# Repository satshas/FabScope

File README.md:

# Fab Scope

An easily fabbable and portable oscilloscope.

Features
--

- 2 voltage range supported: 0-5V, 0-50V (DC only)
- button to change the voltage ranges and fit using interrupts
- supported sampling frequency: from 100HZ to 10KHZ
- adjustable sampling frequency using a potentiometer
- 128 x 64 graphic display
- embedded high voltage relays
- on/off switch
- plug and play probes
- portable (9V battery last for more than 8 hours)
- mdf and acrylic cases
- programmable using an FTDI
- voltage measurements: max, min, average
- fit function that will zoom exactly into the current signal range

Board
--

- [Fab12 scope schematic](https://github.com/satshas/FabScope/raw/master/eagle/fab_scope.sch)
- [Fab12 scope board](https://github.com/satshas/FabScope/raw/master/eagle/fab_scope.brd)
- [Fab12 scope internal png](https://github.com/satshas/FabScope/raw/master/media/fab_scope_internal.png)
- [Fab12 scope cut png](https://github.com/satshas/FabScope/raw/master/media/fab_scope_cut.png)

Software
--

[download the code](https://raw.githubusercontent.com/satshas/FabScope/master/code/fab_scope/fab_scope.ino)

Media
--

Authors
--

- Daniele Ingrassia

Contact
--

- **ingrassiada@gmail.com**
- **[linkedin](http://it.linkedin.com/in/danieleingrassia)**

Thanks
--

[Fablab Kamp-Lintfort](http://fablab.hochschule-rhein-waal.de/index.php/de/)<br />
Hochschule Rhein-Waal<br />
Friedrich-Heinrich-Allee 25, 47475 Kamp-Lintfort, Germany<br />
fablab@hochschule-rhein-waal.de

License
--
This work is licensed under the terms of Attribution-ShareAlike 4.0 International ([CC BY-SA 4.0](https://creativecommons.org/licenses/by-sa/4.0/)).

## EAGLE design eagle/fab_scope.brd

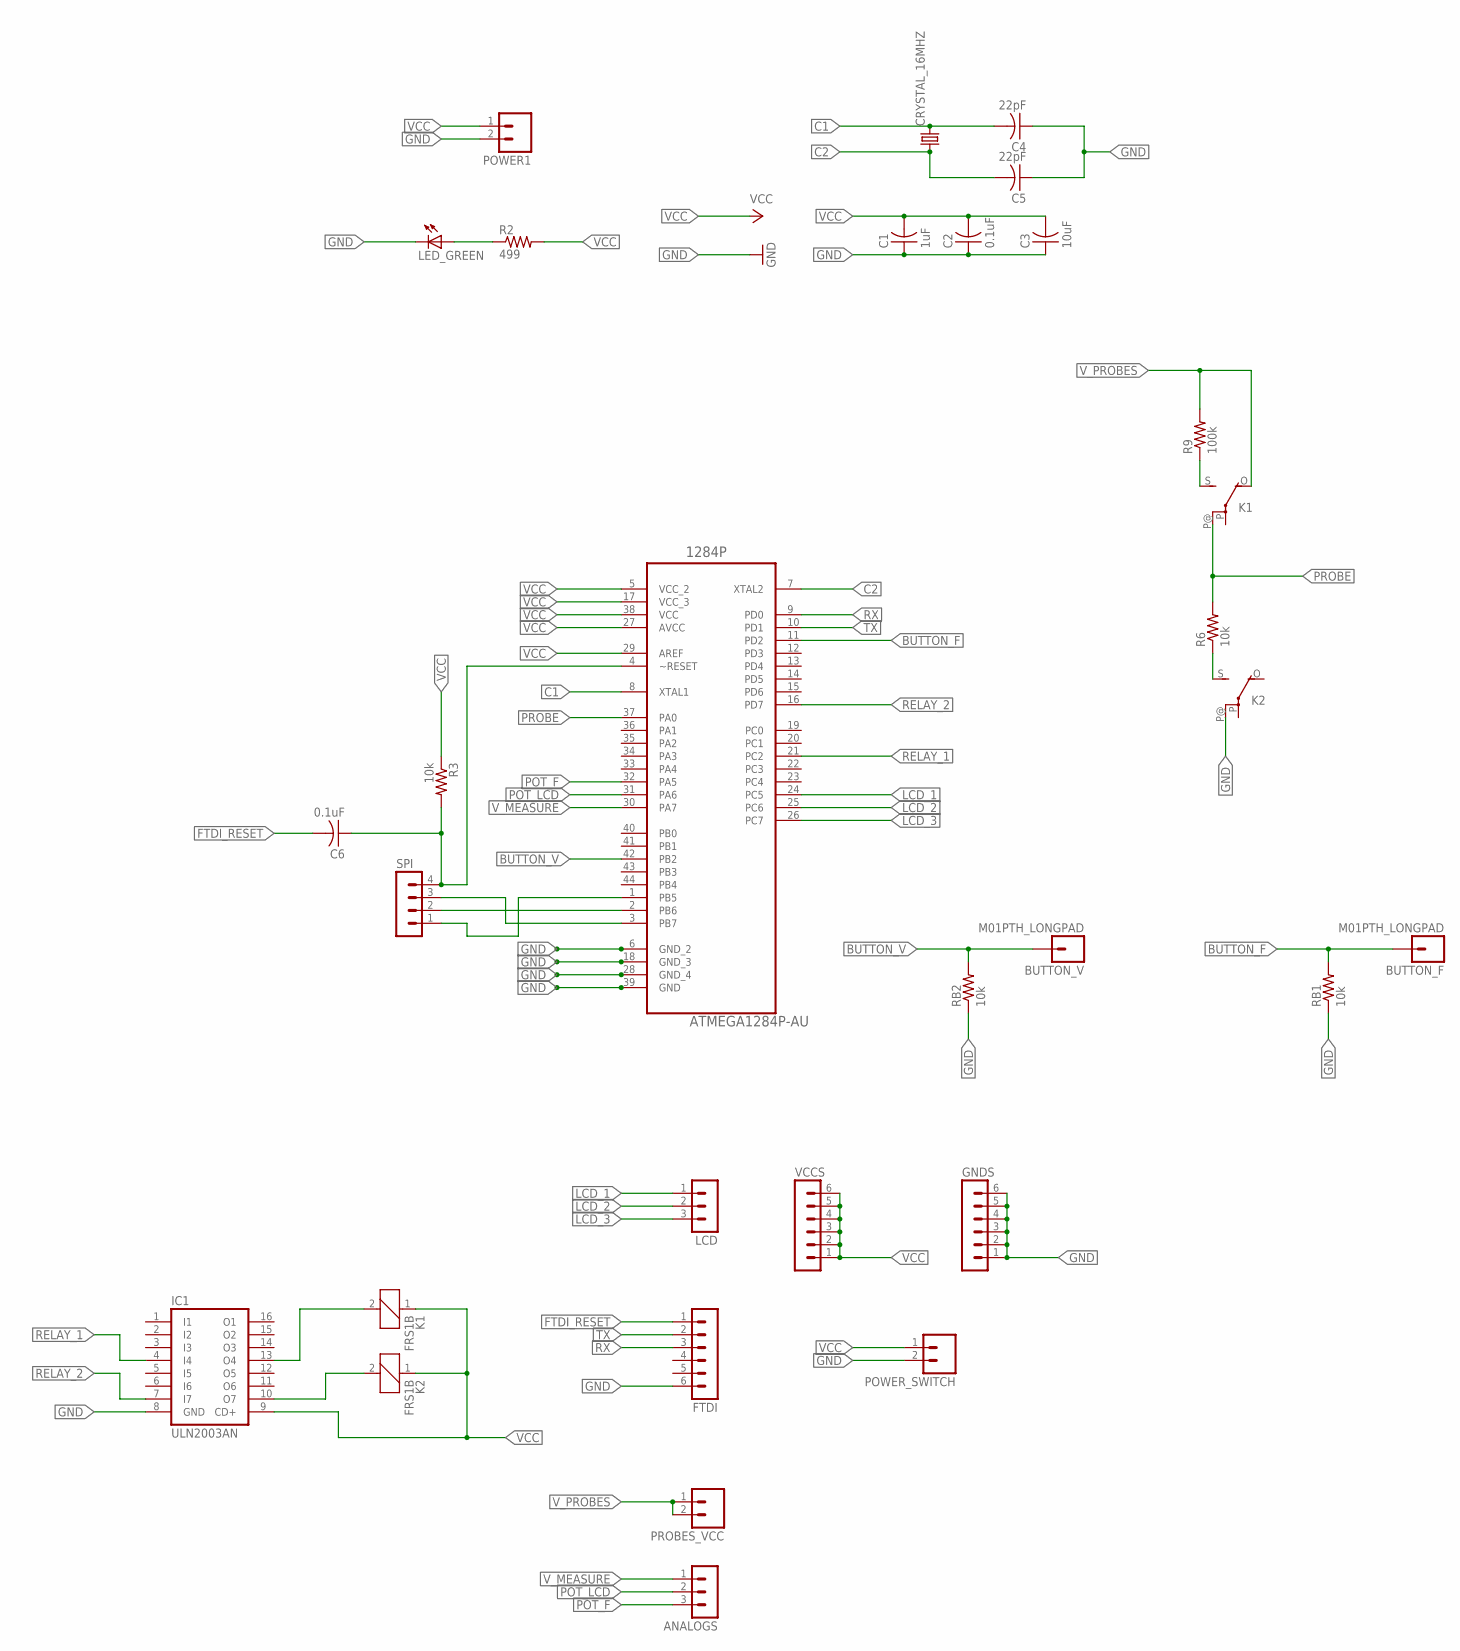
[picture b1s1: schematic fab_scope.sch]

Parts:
1284P: ATMEGA1284P-AU; QFP80P1200X1200X120-44N
ANALOGS: MA03-1
BUTTON_F: M01PTH_LONGPAD; 1X01_LONGPAD
BUTTON_V: M01PTH_LONGPAD; 1X01_LONGPAD
C1: 1uF; C1206
C2, C6: 0.1uF; C1206
C3: 10uF; C1206
C4, C5: 22pF; C1206
CRYSTAL_16MHZ: CRYSTALHC49UP; HC49UP
FTDI: MA06-1
GNDS: MA06-1
IC1: ULN2003AN; DIL16
K1, K2: FRS1B
LCD: MA03-1
LED_GREEN: LED1206; 1206
POWER1: M02; 02P
POWER_SWITCH: M02; 02P
PROBES_VCC: M02; 02P
R2: 499; R1206
R3, R6: 10k; R1206
R9: 100k; R1206
RB1, RB2: 10k; R1206
SPI: MA04-1
VCCS: MA06-1

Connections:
BUTTON_F: 1284P.11 (PD2), BUTTON_F.1, RB1.2
BUTTON_V: 1284P.42 (PB2), BUTTON_V.1, RB2.2
C1: 1284P.8 (XTAL1), C4.2, CRYSTAL_16MHZ.2
C2: 1284P.7 (XTAL2), C5.2, CRYSTAL_16MHZ.1
FTDI_RESET: C6.2, FTDI.1
GND: 1284P.6 (GND_2), C1.1, C2.1, C3.1, C4.1, C5.1, FTDI.6, GNDS.1, GNDS.2, GNDS.3, GNDS.4, GNDS.5, GNDS.6, IC1.8 (GND), K2.P@, LED_GREEN.2 (C), POWER1.2, POWER_SWITCH.2, RB1.1, RB2.1
LCD_1: 1284P.24 (PC5), LCD.1
LCD_2: 1284P.25 (PC6), LCD.2
LCD_3: 1284P.26 (PC7), LCD.3
unnamed: IC1.10 (O7), K2.2
unnamed: IC1.13 (O4), K1.2
unnamed: K2.S, R6.1
unnamed: K1.S, R9.1
unnamed: 1284P.3 (PB7), SPI.3
unnamed: 1284P.2 (PB6), SPI.2
unnamed: 1284P.1 (PB5), SPI.1
unnamed: 1284P.4 (~RESET), C6.1, R3.2, SPI.4
unnamed: LED_GREEN.1 (A), R2.1
POT_F: 1284P.32 (PA5), ANALOGS.3
POT_LCD: 1284P.31 (PA6), ANALOGS.2
PROBE: 1284P.37 (PA0), K1.P@, R6.2
RELAY_1: 1284P.21 (PC2), IC1.4 (I4)
RELAY_2: 1284P.16 (PD7), IC1.7 (I7)
RX: 1284P.9 (PD0), FTDI.3
TX: 1284P.10 (PD1), FTDI.2
VCC: 1284P.5 (VCC_2), 1284P.17 (VCC_3), 1284P.27 (AVCC), 1284P.29 (AREF), C1.2, C2.2, C3.2, IC1.9 (CD+), K1.1, K2.1, POWER1.1, POWER_SWITCH.1, R2.2, R3.1, VCCS.1, VCCS.2, VCCS.3, VCCS.4, VCCS.5, VCCS.6
V_MEASURE: 1284P.30 (PA7), ANALOGS.1
V_PROBES: K1.O, PROBES_VCC.1, PROBES_VCC.2, R9.2

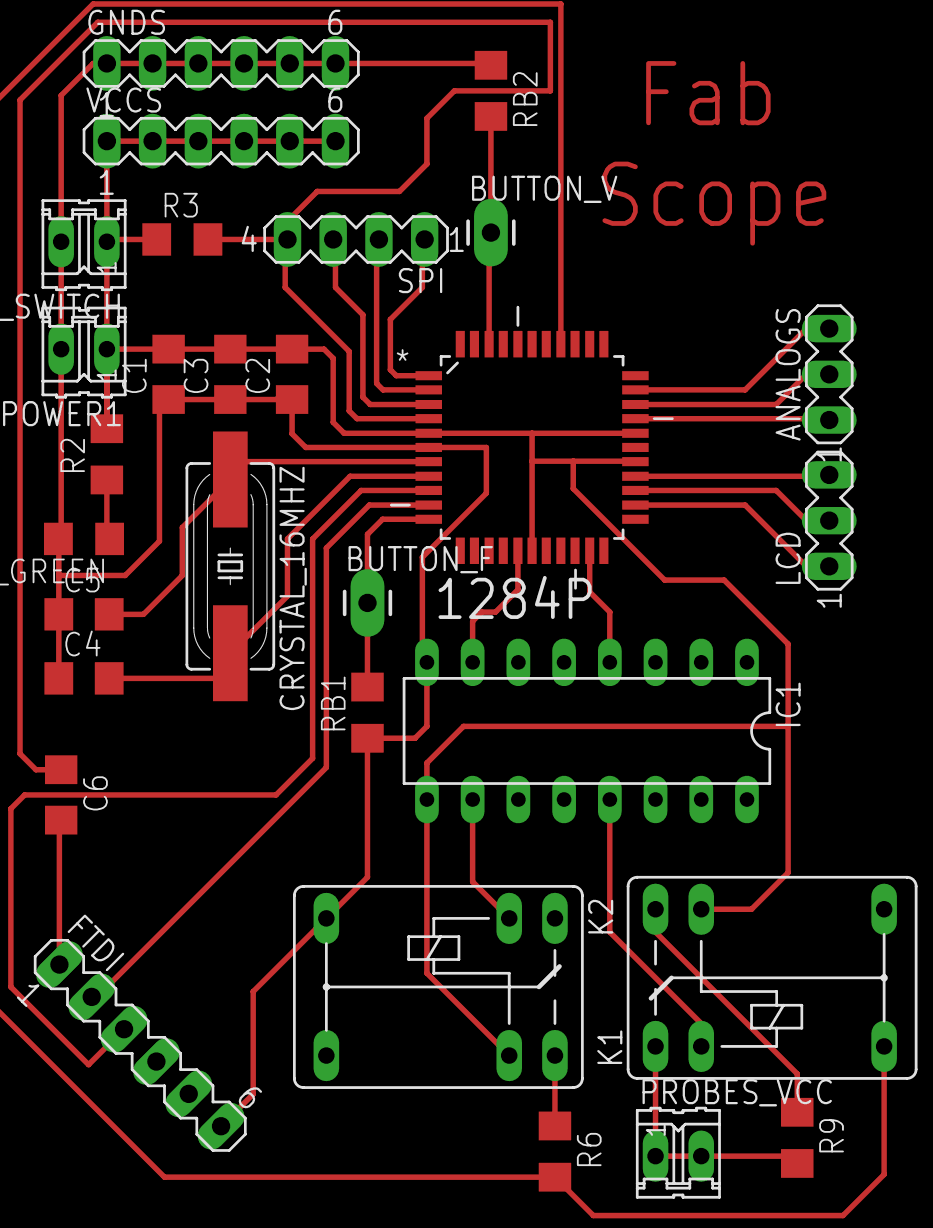
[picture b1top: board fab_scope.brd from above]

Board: 2 copper layers, 29 parts (0 on the bottom side), 28 nets.

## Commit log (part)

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2016-06-08 added sketch
2016-06-14 added images and code about the first prototype
2016-06-22 added new scope version
2016-06-22 updated bom
2016-06-27 added design and updated bom
2016-06-28 third prototype done
2016-06-29 readem fix
2016-06-29 readme fixes
2016-08-02 added the final version of the code
2016-08-02 added some media
2017-07-21 added the proper license
2017-08-09 added new board and imgs
2017-08-09 fixed links and added imgs
2017-08-09 fixed links
2017-08-09 added the new code
2017-08-09 fixed code link
2017-08-09 added media
2017-08-09 added bom and design

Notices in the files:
parts and their libraries:
01_SparkFun: Licensing: CC v3.0 Share-Alike You are welcome to use this library for commercial purposes.
